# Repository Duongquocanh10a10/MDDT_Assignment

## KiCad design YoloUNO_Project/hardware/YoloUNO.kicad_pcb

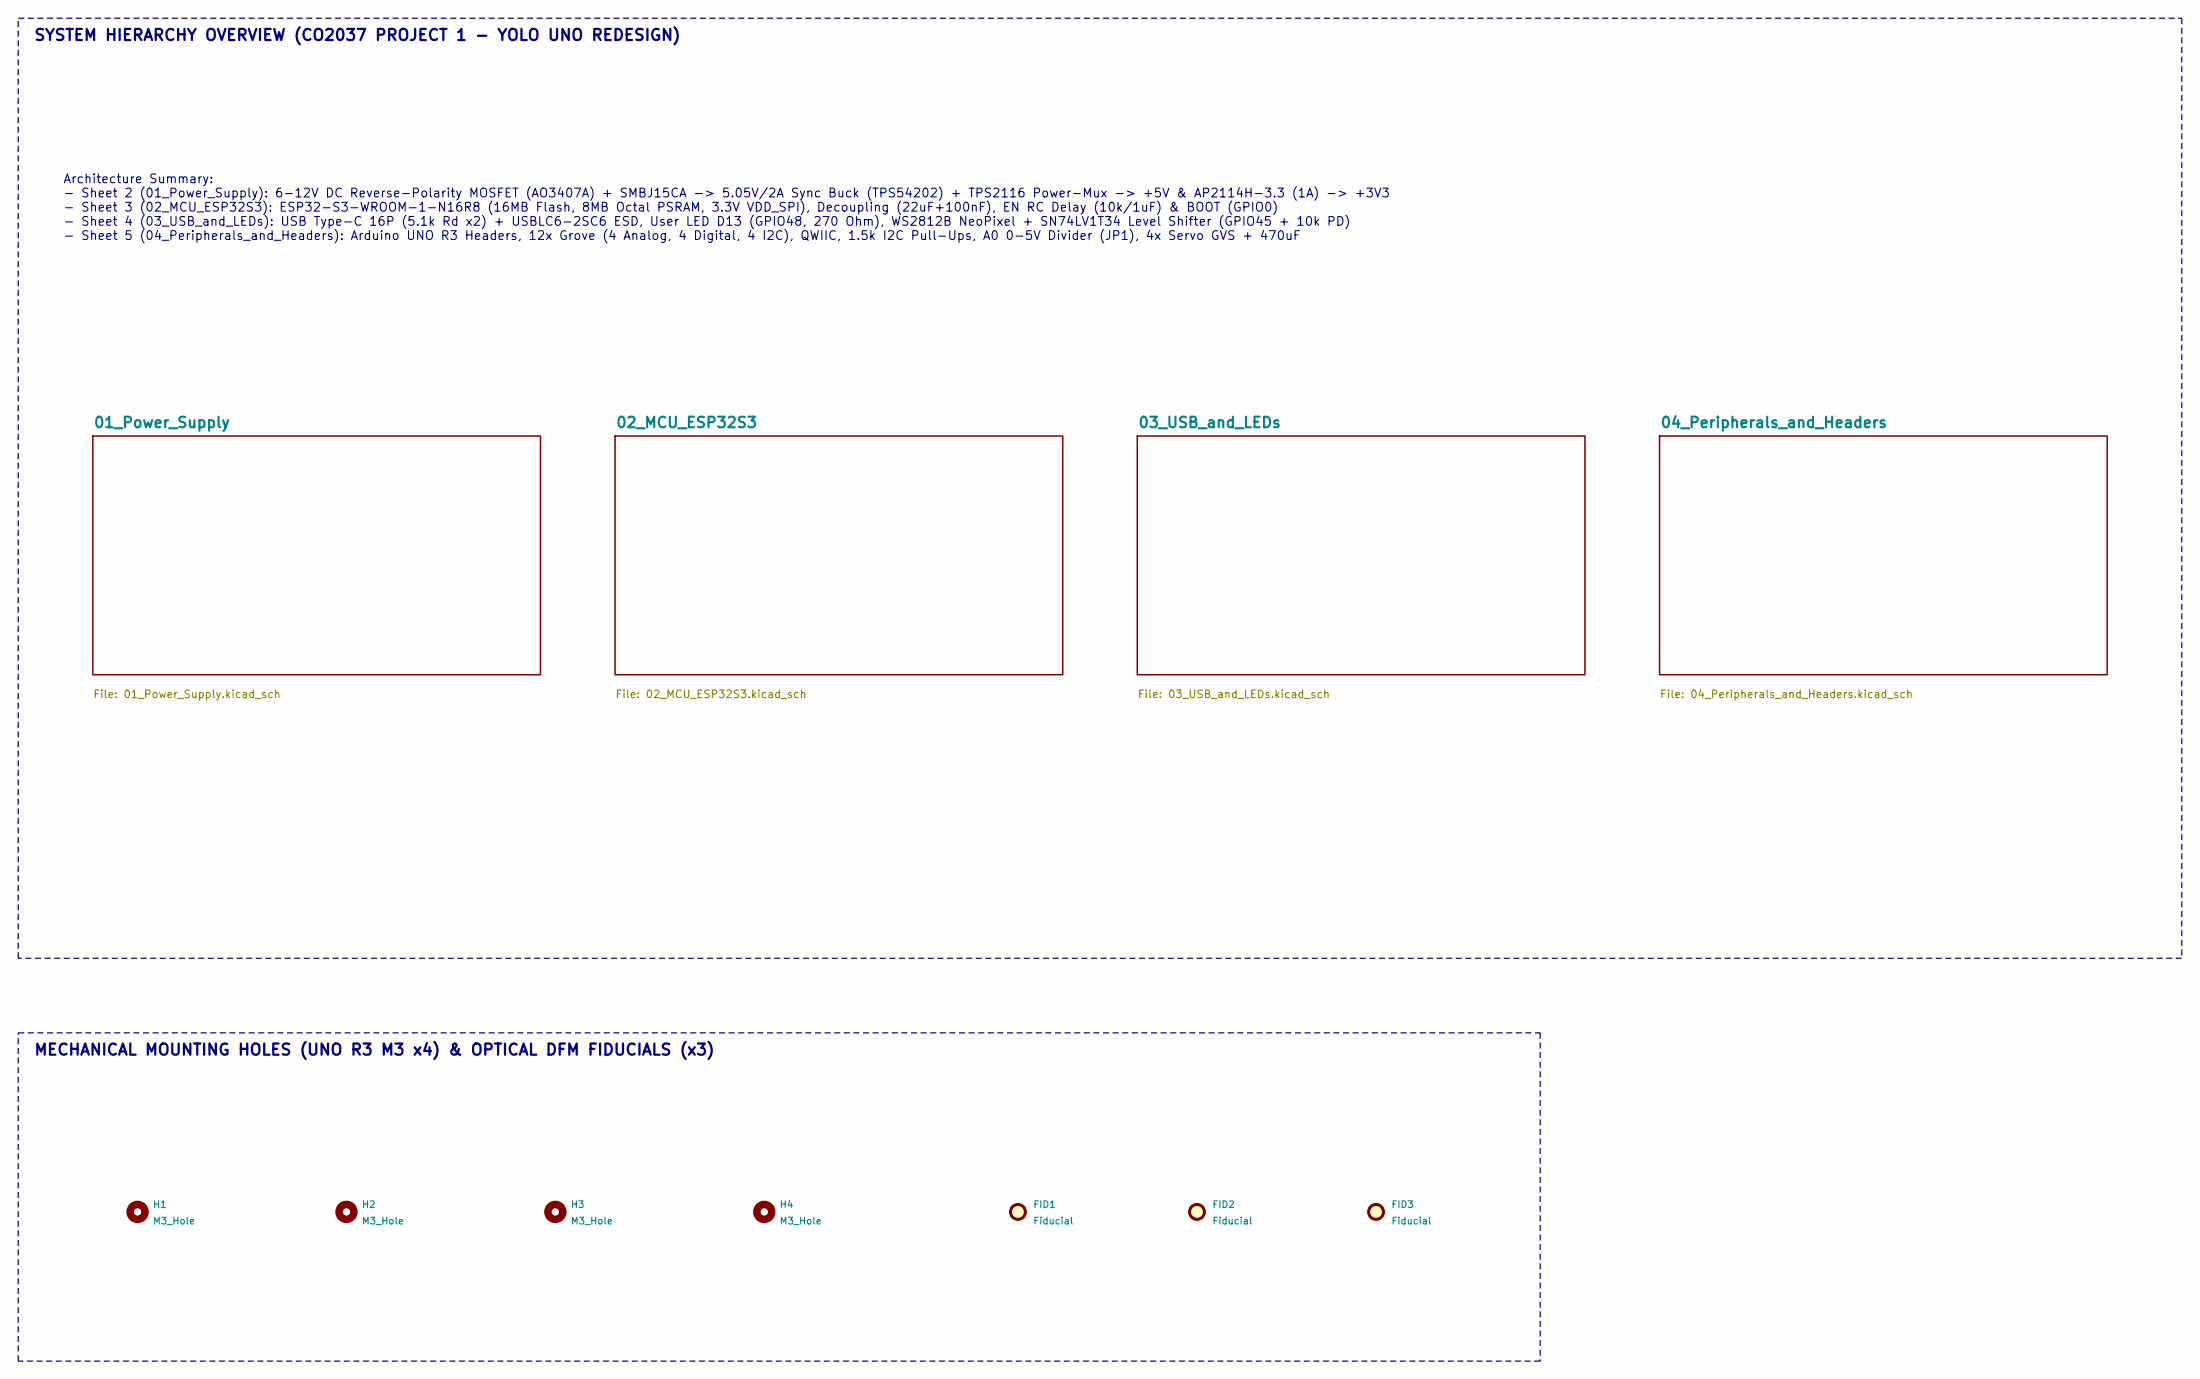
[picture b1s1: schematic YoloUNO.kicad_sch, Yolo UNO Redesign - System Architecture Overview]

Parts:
FID1, FID2, FID3: Fiducial; Fiducial_1mm_Mask2mm; MPN FIDUCIAL_1MM; LCSC N/A
H1, H2, H3, H4: M3_Hole; MountingHole_3.2mm_M3; MPN M3_NPTH_UNO_R3; LCSC N/A

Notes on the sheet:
SYSTEM HIERARCHY OVERVIEW (CO2037 PROJECT 1 - YOLO UNO REDESIGN)
Architecture Summary: - Sheet 2 (01_Power_Supply): 6-12V DC Reverse-Polarity MOSFET (AO3407A) + SMBJ15CA -> 5.05V/2A Sync Buck (TPS54202) + TPS2116 Power-Mux -> +5V & AP2114H-3.3 (1A) -> +3V3 - Sheet 3 (02_MCU_ESP32S3): ESP32-S3-WROOM-1-N16R8 (16MB Flash, 8MB Octal PSRAM, 3.3V VDD_SPI), Decoupling 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
MECHANICAL MOUNTING HOLES (UNO R3 M3 x4) & OPTICAL DFM FIDUCIALS (x3)

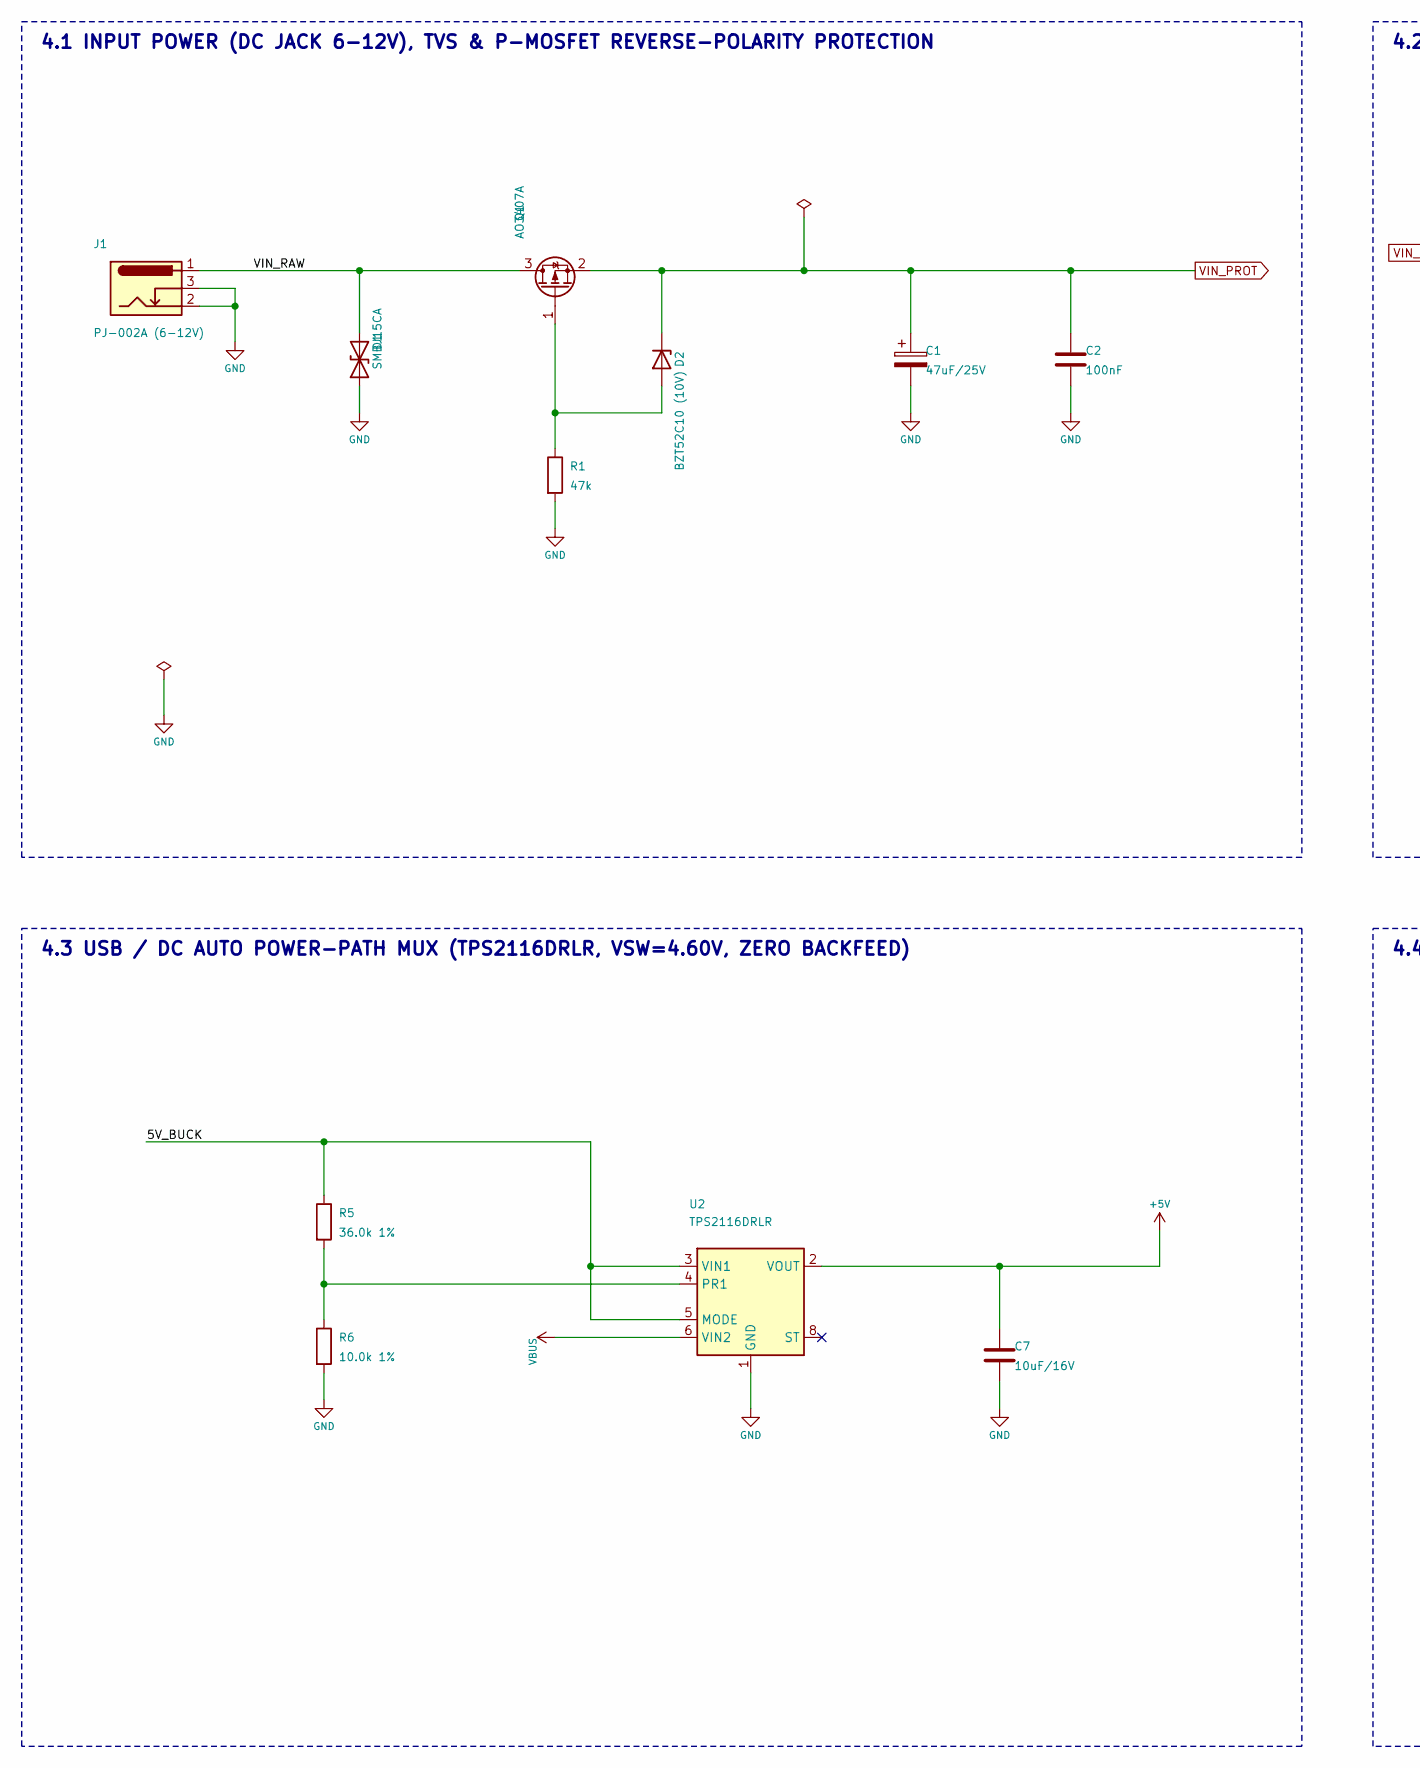
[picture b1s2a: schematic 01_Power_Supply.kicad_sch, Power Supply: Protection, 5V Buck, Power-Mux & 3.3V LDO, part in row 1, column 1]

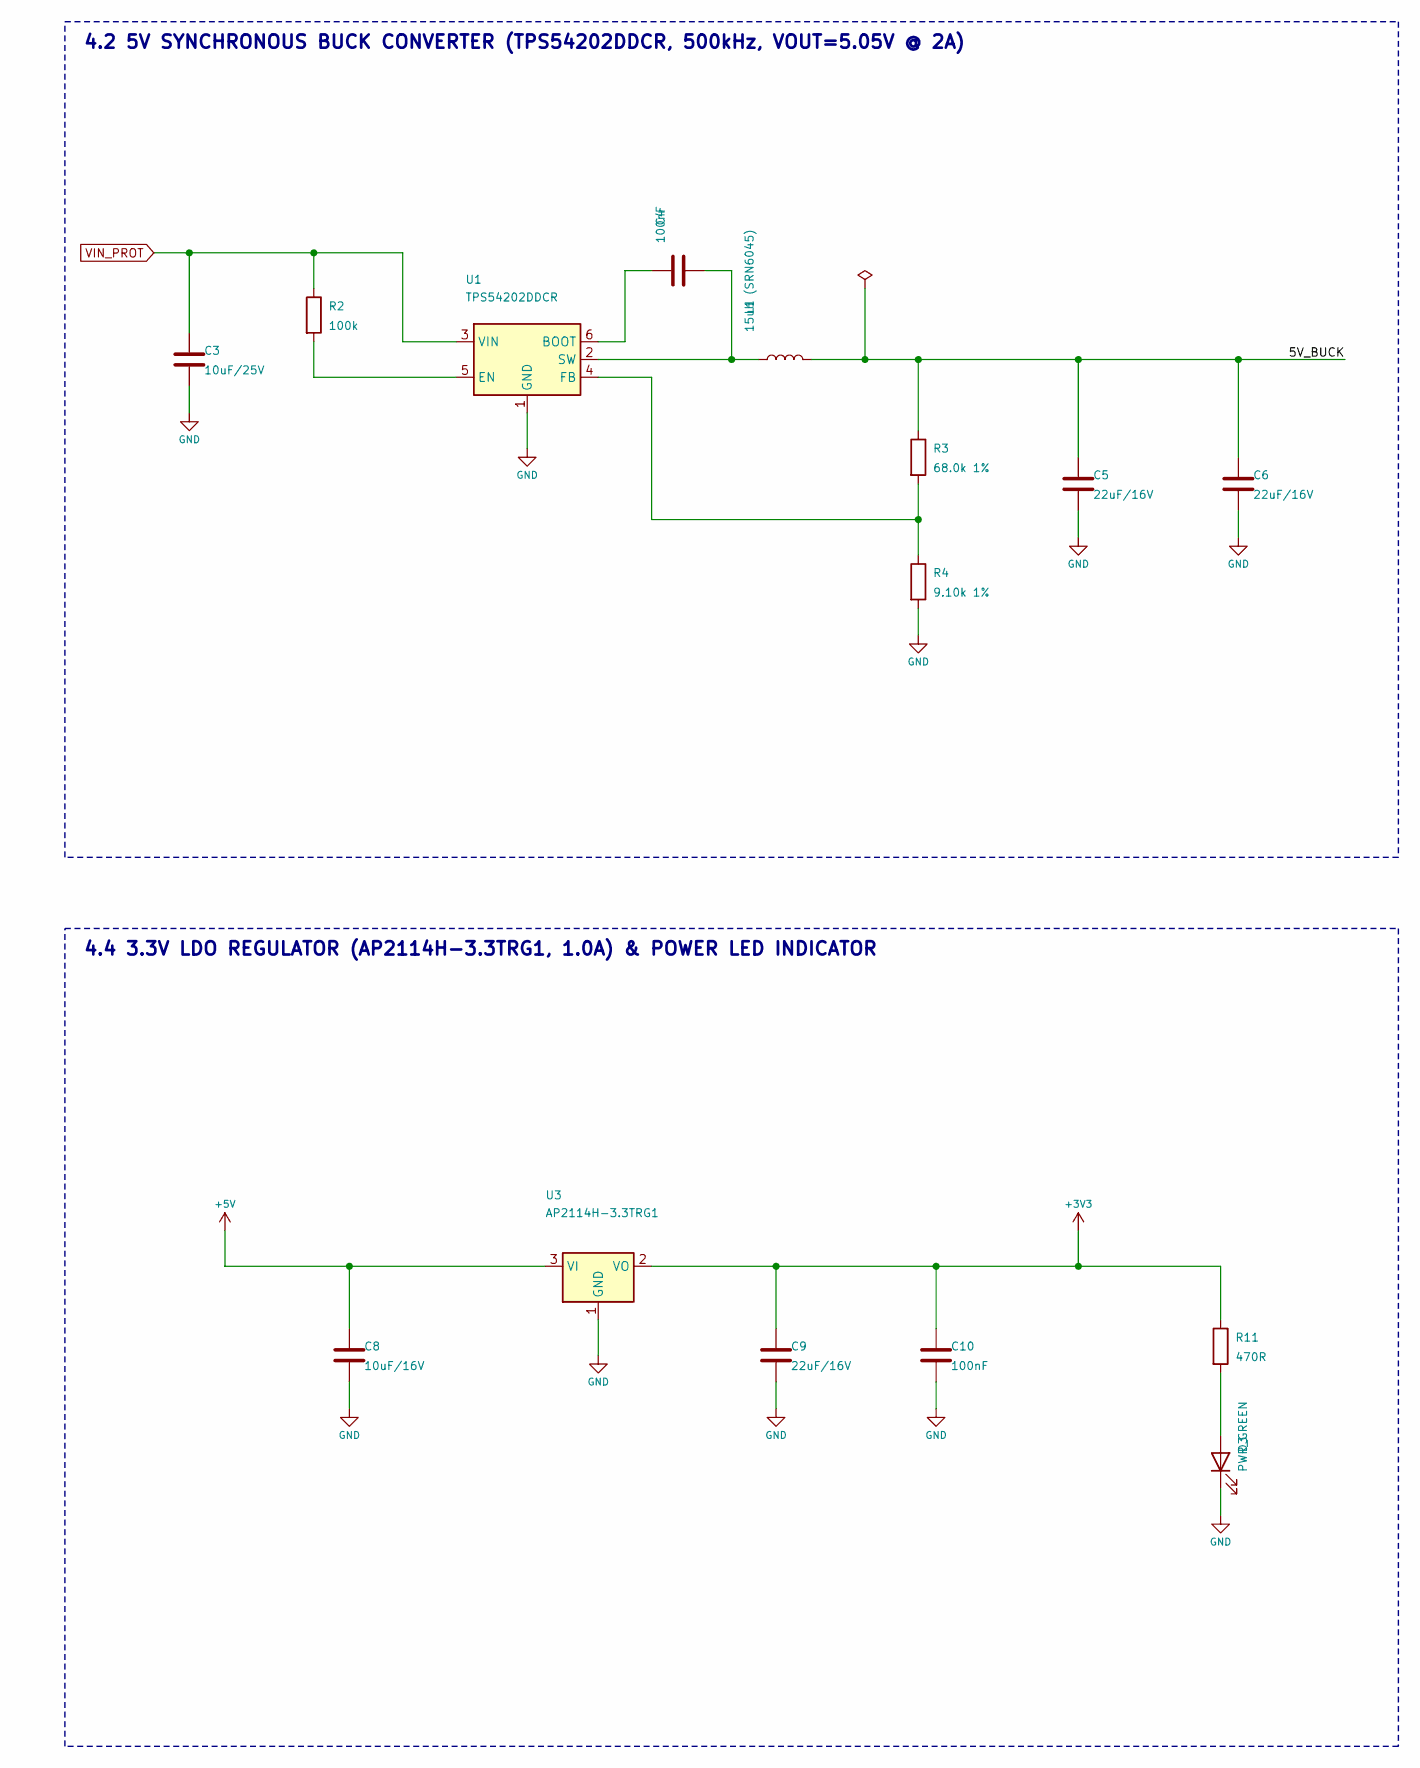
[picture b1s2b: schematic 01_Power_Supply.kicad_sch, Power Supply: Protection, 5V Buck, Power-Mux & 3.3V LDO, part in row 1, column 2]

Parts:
C1: 47uF/25V; CP_Elec_6.3x5.4; MPN EEE-FK1E470P; LCSC C72485
C2, C4, C10: 100nF; C_0603_1608Metric; MPN CL10B104KB8NNNC; LCSC C1591
C3: 10uF/25V; C_0805_2012Metric; MPN GRM21BR61E106KA73L; LCSC C15850
C5, C6, C9: 22uF/16V; C_0805_2012Metric; MPN GRM21BR61C226ME44L; LCSC C45783
C7, C8: 10uF/16V; C_0805_2012Metric; MPN CL21A106KOQNNNE; LCSC C17024
D1: SMBJ15CA; D_SMB; MPN SMBJ15CA; LCSC C123785
D2: BZT52C10 (10V); D_SOD-123; MPN BZT52C10-7-F; LCSC C81598
D3: PWR_GREEN; LED_0603_1608Metric; MPN 19-217/GHC-YR1S2/3T; LCSC C72043
J1: PJ-002A (6-12V); BarrelJack_CUI_PJ-102AH_Horizontal; MPN PJ-002A; LCSC C720477
L1: 15uH (SRN6045); L_Bourns_SRN6045TA; MPN SRN6045TA-150M; LCSC C169400
Q1: AO3407A; SOT-23-3; MPN AO3407A; LCSC C347475
R1: 47k; R_0603_1608Metric; MPN RC0603FR-0747KL; LCSC C25819
R2: 100k; R_0603_1608Metric; MPN RC0603FR-07100KL; LCSC C25803
R3: 68.0k 1%; R_0603_1608Metric; MPN RC0603FR-0768KL; LCSC C23231
R4: 9.10k 1%; R_0603_1608Metric; MPN RC0603FR-079K1L; LCSC C23268
R5: 36.0k 1%; R_0603_1608Metric; MPN RC0603FR-0736KL; LCSC C23146
R6: 10.0k 1%; R_0603_1608Metric; MPN RC0603FR-0710KL; LCSC C25804
R11: 470R; R_0603_1608Metric; MPN RC0603FR-07470RL; LCSC C23179
U1: TPS54202DDCR; SOT-23-6; MPN TPS54202DDCR; LCSC C128249
U2: TPS2116DRLR; SOT-583-8; MPN TPS2116DRLR; LCSC C2875184
U3: AP2114H-3.3TRG1; SOT-223-3_TabPin2; MPN AP2114H-3.3TRG1; LCSC C151275

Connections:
+3V3: C9.1, C10.1, R11.1, U3.2 (VO); also elsewhere on the board
+5V: C7.1, C8.1, U2.2 (VOUT), U2.7 (VOUT), U3.3 (VI); also elsewhere on the board
/01_Power_Supply/5V_BUCK: C5.1, C6.1, L1.2, R3.1, R5.1, U2.3 (VIN1), U2.5 (MODE)
/01_Power_Supply/VIN_RAW: D1.2 (A2), J1.1, Q1.3 (D)
unnamed: D2.2 (A), Q1.1 (G), R1.1
unnamed: D3.2 (A), R11.2
unnamed: C4.1, U1.6 (BOOT)
unnamed: R2.2, U1.5 (EN)
unnamed: R3.2, R4.1, U1.4 (FB)
unnamed: C4.2, L1.1, U1.2 (SW)
unnamed: R5.2, R6.1, U2.4 (PR1)
VBUS: U2.6 (VIN2); also elsewhere on the board
VIN_PROT: C1.1, C2.1, C3.1, D2.1 (K), Q1.2 (S), R2.1, U1.3 (VIN); also elsewhere on the board

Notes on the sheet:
4.1 INPUT POWER (DC JACK 6-12V), TVS & P-MOSFET REVERSE-POLARITY PROTECTION
4.2 5V SYNCHRONOUS BUCK CONVERTER (TPS54202DDCR, 500kHz, VOUT=5.05V @ 2A)
4.3 USB / DC AUTO POWER-PATH MUX (TPS2116DRLR, VSW=4.60V, ZERO BACKFEED)
4.4 3.3V LDO REGULATOR (AP2114H-3.3TRG1, 1.0A) & POWER LED INDICATOR

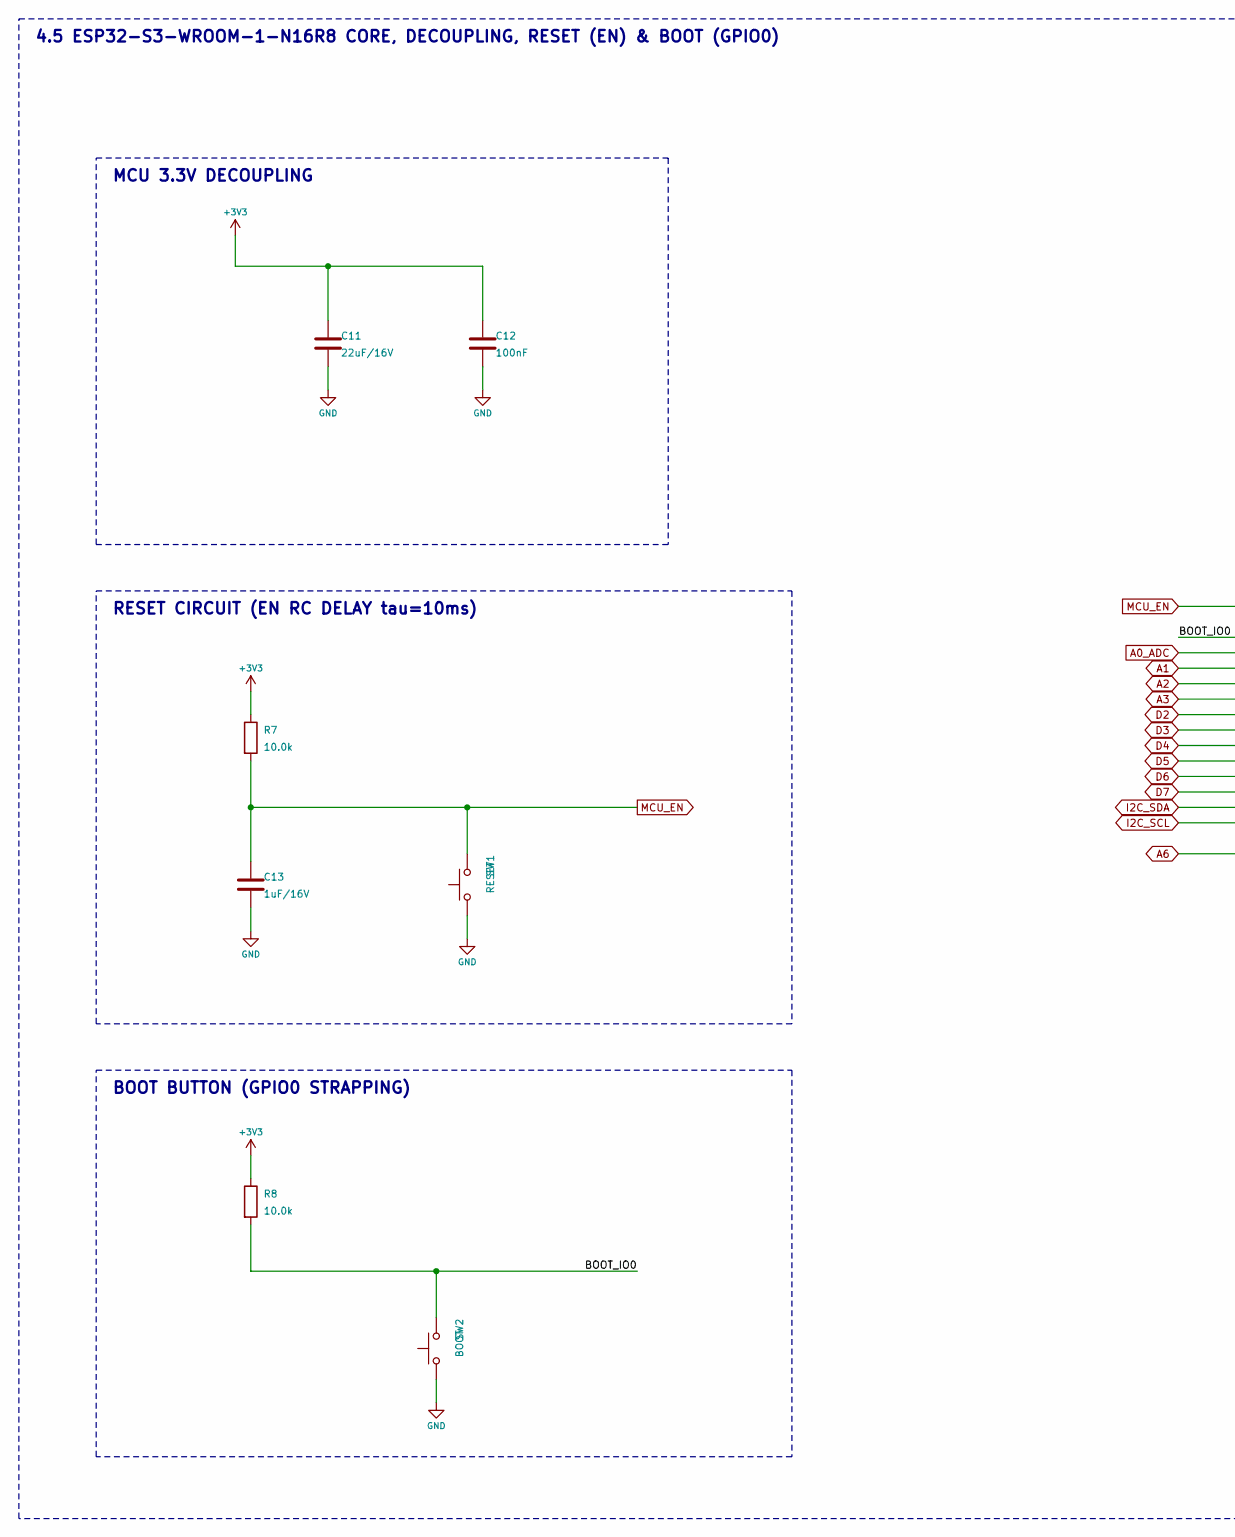
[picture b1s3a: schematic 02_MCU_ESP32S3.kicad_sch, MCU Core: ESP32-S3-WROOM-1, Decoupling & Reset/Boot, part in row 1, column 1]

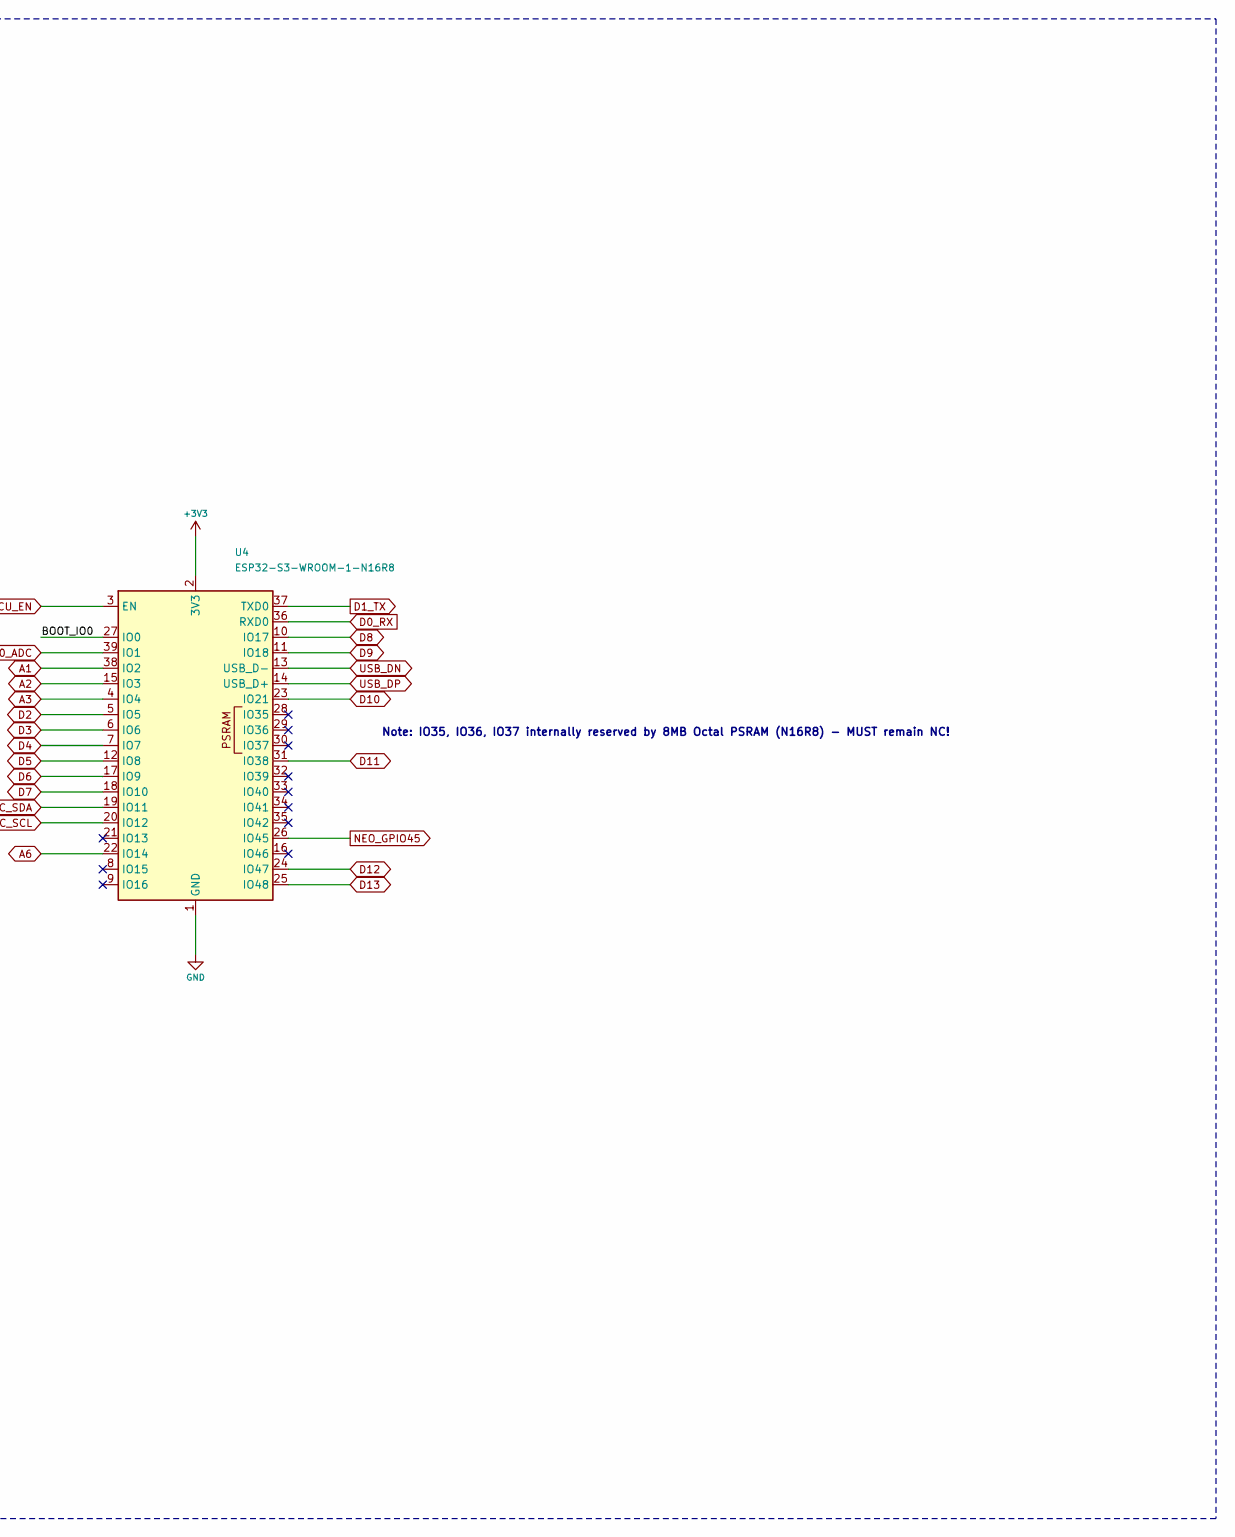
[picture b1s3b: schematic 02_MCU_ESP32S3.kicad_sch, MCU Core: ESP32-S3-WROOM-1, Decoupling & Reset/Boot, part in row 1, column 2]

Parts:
C11: 22uF/16V; C_0805_2012Metric; MPN GRM21BR61C226ME44L; LCSC C45783
C12: 100nF; C_0603_1608Metric; MPN CL10B104KB8NNNC; LCSC C1591
C13: 1uF/16V; C_0603_1608Metric; MPN CL10B105KO8NNNC; LCSC C15849
R7, R8: 10.0k; R_0603_1608Metric; MPN RC0603FR-0710KL; LCSC C25804
SW1: RESET; SW_Push_1P1T_XKB_TS-1187A; MPN TS-1187A-B-A-B; LCSC C318884
SW2: BOOT; SW_Push_1P1T_XKB_TS-1187A; MPN TS-1187A-B-A-B; LCSC C318884
U4: ESP32-S3-WROOM-1-N16R8; ESP32-S3-WROOM-1; MPN ESP32-S3-WROOM-1-N16R8; LCSC C2913202

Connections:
+3V3: C11.1, C12.1, R7.1, R8.1, U4.2 (3V3); also elsewhere on the board
/02_MCU_ESP32S3/BOOT_IO0: R8.2, SW2.2, U4.27 (IO0)
A0_ADC: U4.39 (IO1); also elsewhere on the board
A1: U4.38 (IO2); also elsewhere on the board
A2: U4.15 (IO3); also elsewhere on the board
A3: U4.4 (IO4); also elsewhere on the board
A6: U4.22 (IO14); also elsewhere on the board
D0_RX: U4.36 (RXD0); also elsewhere on the board
D1_TX: U4.37 (TXD0); also elsewhere on the board
D2: U4.5 (IO5); also elsewhere on the board
D3: U4.6 (IO6); also elsewhere on the board
D4: U4.7 (IO7); also elsewhere on the board
D5: U4.12 (IO8); also elsewhere on the board
D6: U4.17 (IO9); also elsewhere on the board
D7: U4.18 (IO10); also elsewhere on the board
D8: U4.10 (IO17); also elsewhere on the board
D9: U4.11 (IO18); also elsewhere on the board
D10: U4.23 (IO21); also elsewhere on the board
D11: U4.31 (IO38); also elsewhere on the board
D12: U4.24 (IO47); also elsewhere on the board
D13: U4.25 (IO48); also elsewhere on the board
I2C_SCL: U4.20 (IO12); also elsewhere on the board
I2C_SDA: U4.19 (IO11); also elsewhere on the board
MCU_EN: C13.1, R7.2, SW1.2, U4.3 (EN); also elsewhere on the board
NEO_GPIO45: U4.26 (IO45); also elsewhere on the board
USB_DN: U4.13 (USB_D-); also elsewhere on the board
USB_DP: U4.14 (USB_D+); also elsewhere on the board

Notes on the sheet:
4.5 ESP32-S3-WROOM-1-N16R8 CORE, DECOUPLING, RESET (EN) & BOOT (GPIO0)
Note: IO35, IO36, IO37 internally reserved by 8MB Octal PSRAM (N16R8) - MUST remain NC!
MCU 3.3V DECOUPLING
RESET CIRCUIT (EN RC DELAY tau=10ms)
BOOT BUTTON (GPIO0 STRAPPING)

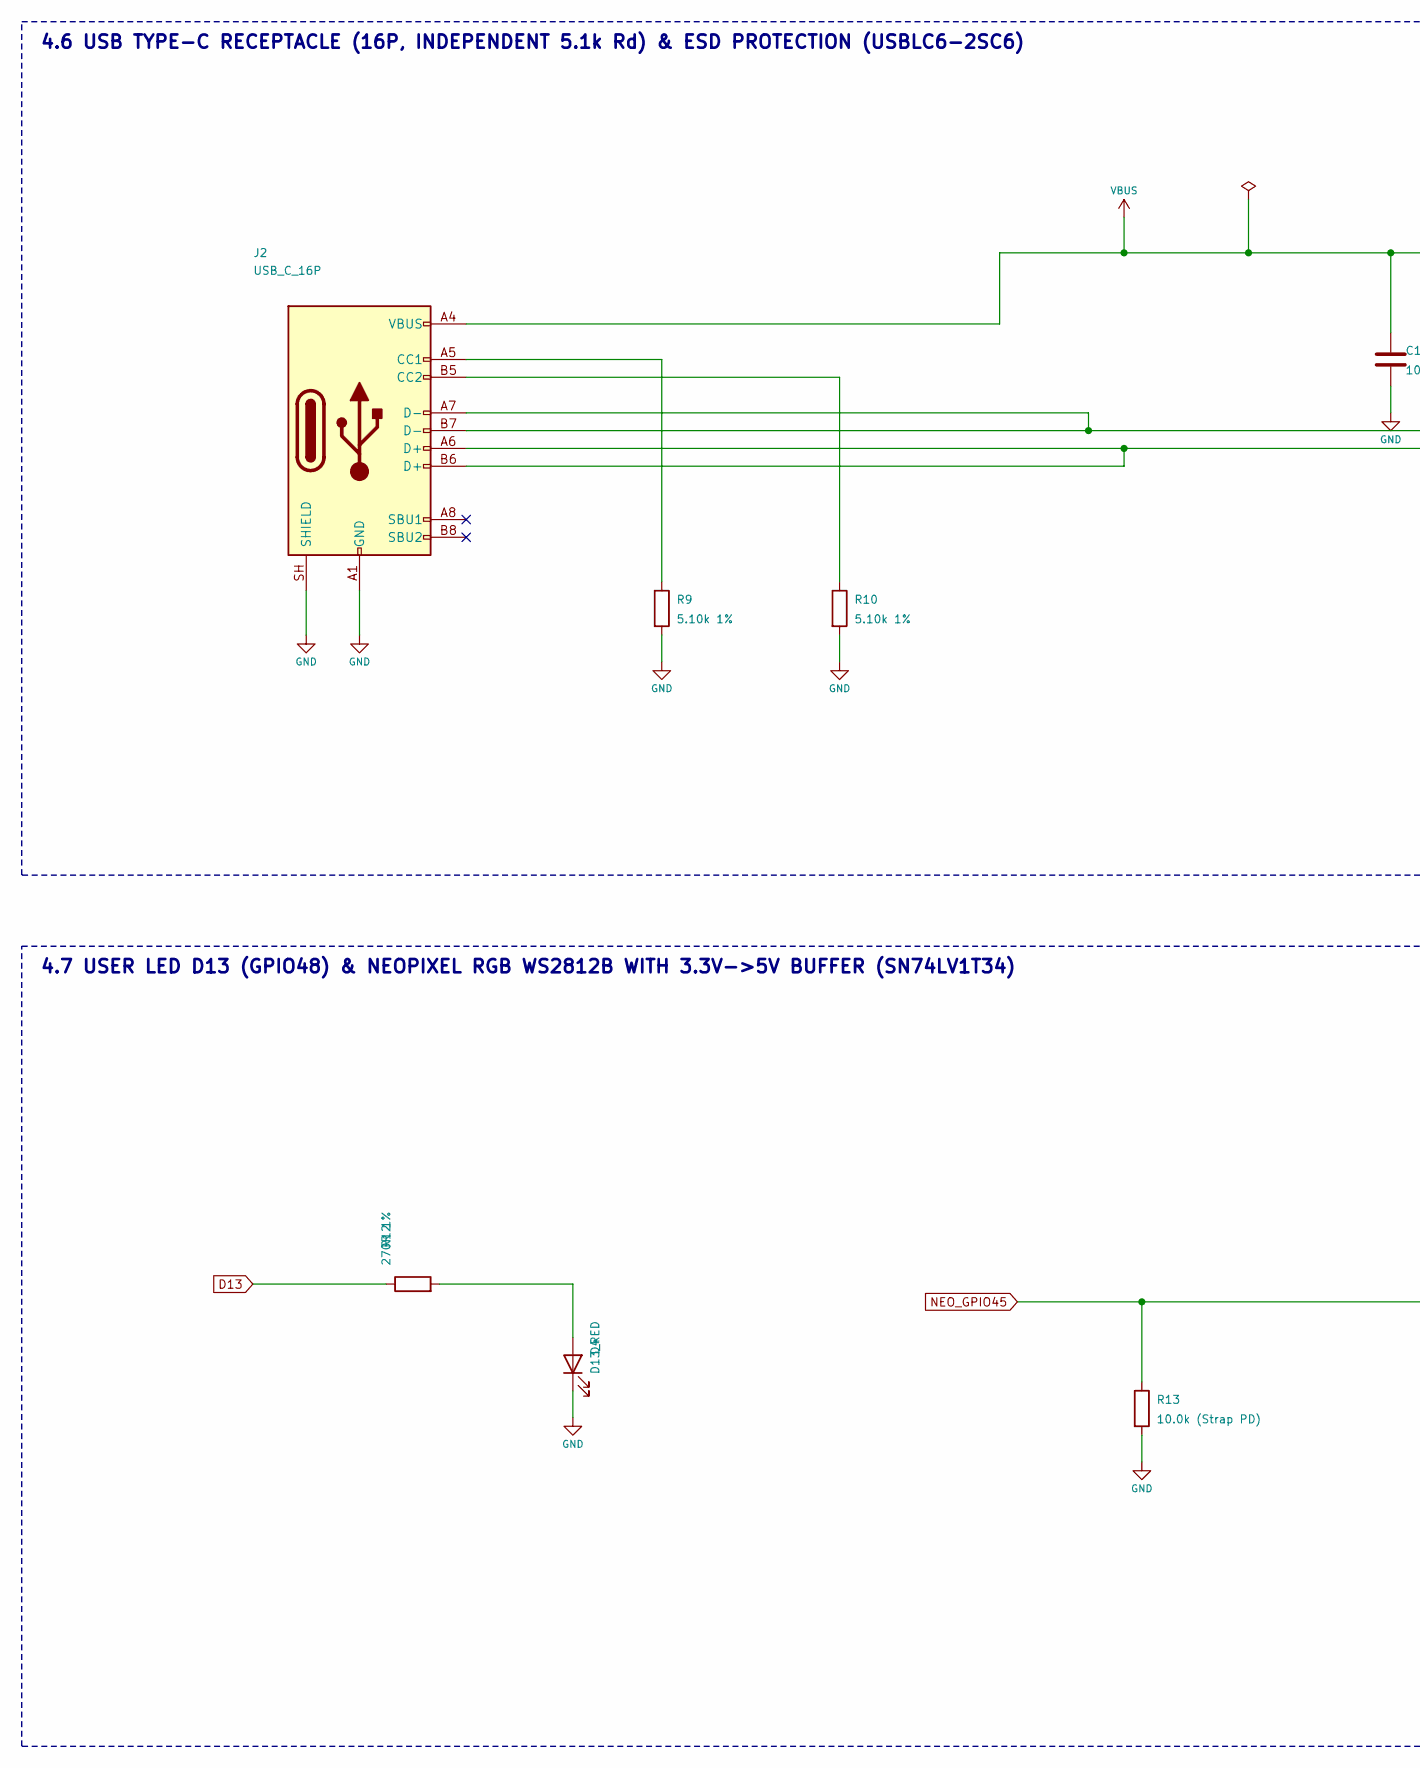
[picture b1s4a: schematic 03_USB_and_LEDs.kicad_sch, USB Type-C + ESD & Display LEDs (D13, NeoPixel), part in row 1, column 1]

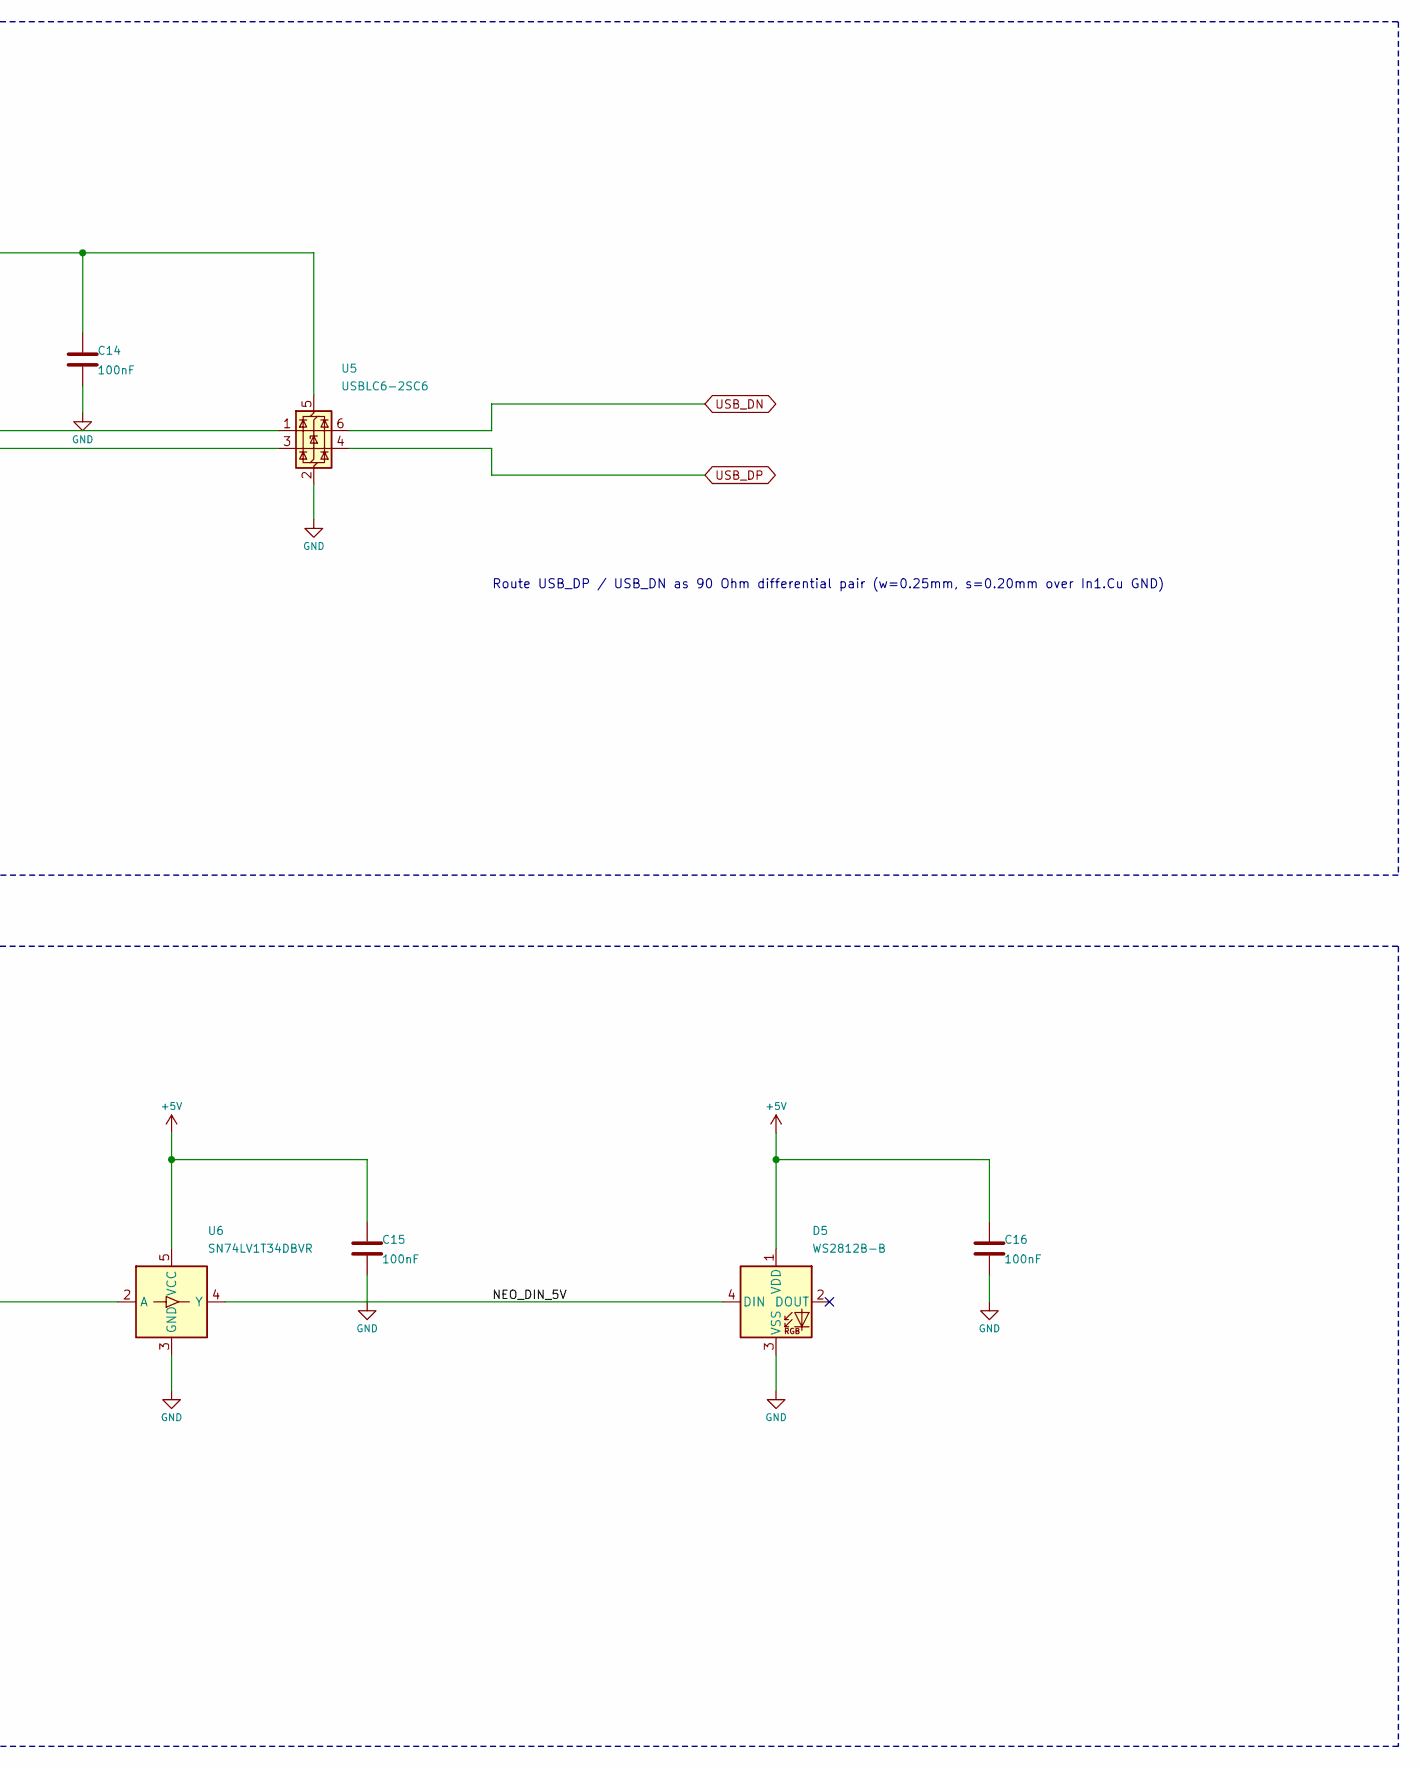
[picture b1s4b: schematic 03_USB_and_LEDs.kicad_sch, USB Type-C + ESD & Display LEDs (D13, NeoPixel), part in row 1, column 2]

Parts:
C14, C15, C16: 100nF; C_0603_1608Metric; MPN CL10B104KB8NNNC; LCSC C1591
D4: D13_RED; LED_0603_1608Metric; MPN 19-217/R6C-AL1M2VY/3T; LCSC C2286
D5: WS2812B-B; LED_WS2812B_PLCC4_5.0x5.0mm_P3.2mm; MPN WS2812B-B/W; LCSC C114586
J2: USB_C_16P; USB_C_Receptacle_HRO_TYPE-C-31-M-12; MPN TYPE-C-31-M-12; LCSC C165948
R9, R10: 5.10k 1%; R_0603_1608Metric; MPN RC0603FR-075K1L; LCSC C23186
R12: 270R 1%; R_0603_1608Metric; MPN RC0603FR-07270RL; LCSC C22966
R13: 10.0k (Strap PD); R_0603_1608Metric; MPN RC0603FR-0710KL; LCSC C25804
U5: USBLC6-2SC6; SOT-23-6; MPN USBLC6-2SC6; LCSC C7519
U6: SN74LV1T34DBVR; SOT-23-5; MPN SN74LV1T34DBVR; LCSC C100018

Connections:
+5V: C15.1, C16.1, D5.1 (VDD), U6.5 (VCC); also elsewhere on the board
D13: R12.1; also elsewhere on the board
NEO_GPIO45: R13.1, U6.2 (A); also elsewhere on the board
unnamed: D4.2 (A), R12.2
unnamed: J2.A5 (CC1), R9.1
unnamed: J2.B5 (CC2), R10.1
unnamed: J2.A6 (D+), J2.B6 (D+), U5.3 (I/O2)
unnamed: J2.A7 (D-), J2.B7 (D-), U5.1 (I/O1)
USB_DN: U5.6 (I/O1); also elsewhere on the board
USB_DP: U5.4 (I/O2); also elsewhere on the board
VBUS: C14.1, J2.A4 (VBUS), J2.A9 (VBUS), J2.B4 (VBUS), J2.B9 (VBUS), U5.5 (VBUS); also elsewhere on the board

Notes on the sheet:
4.6 USB TYPE-C RECEPTACLE (16P, INDEPENDENT 5.1k Rd) & ESD PROTECTION (USBLC6-2SC6)
Route USB_DP / USB_DN as 90 Ohm differential pair (w=0.25mm, s=0.20mm over In1.Cu GND)
4.7 USER LED D13 (GPIO48) & NEOPIXEL RGB WS2812B WITH 3.3V->5V BUFFER (SN74LV1T34)

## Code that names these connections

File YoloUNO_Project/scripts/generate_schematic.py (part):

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                 68.58, 68.58, rot=90, mpn="SMBJ15CA", lcsc="C123785",
                 ref_offset=(2.54, -1.27), val_offset=(2.54, 1.524))
s_pwr.add_wire(j1_p1[0], j1_p1[1], 68.58, j1_p1[1])
s_pwr.add_label("VIN_RAW", 53.34, j1_p1[1])
s_pwr.add_wire(68.58, j1_p1[1], *d1.pin_xy("2"))
s_pwr.add_junction(68.58, j1_p1[1])
s_pwr.tie_gnd(*d1.pin_xy("1"), 3.81)
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s_pwr.add_junction(170.18, 55.88)
s_pwr.tie_gnd(*c2.pin_xy("2"), 3.81)

s_pwr.add_glabel("VIN_PROT", 187.96, 55.88, rot=0, shape="output")

s_pwr.add_pwr("GND", 40.64, 119.38, rot=0)
s_pwr.add_wire(40.64, 119.38, 40.64, 114.3)
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u1_sw = u1.pin_xy("2")
u1_fb = u1.pin_xy("4")

s_pwr.add_glabel("VIN_PROT", 226.06, 53.34, rot=180, shape="input")
s_pwr.add_wire(226.06, 53.34, 261.62, 53.34)
s_pwr.add_wire(261.62, 53.34, 261.62, u1_vin[1])
s_pwr.add_wire(261.62, u1_vin[1], u1_vin[0], u1_vin[1])
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    "14": ("USB_DP", "bidirectional"),
    "23": ("D10", "bidirectional"),
    "31": ("D11", "bidirectional"),
    "26": ("NEO_GPIO45", "output"),
    "24": ("D12", "bidirectional"),
    "25": ("D13", "bidirectional"),
}
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en_y = 149.86
s_mcu.add_wire(*r7.pin_xy("2"), 58.42, en_y)
s_mcu.add_wire(58.42, en_y, 121.92, en_y)
s_mcu.add_glabel("MCU_EN", 121.92, en_y, rot=0, shape="output")

c13 = s_mcu.place("YoloUNO:C", "C13", "1uF/16V", "YoloUNO:C_0603_1608Metric",
                  58.42, 162.56, rot=0, mpn="CL10B105KO8NNNC", lcsc="C15849")
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boot_y = 226.06
s_mcu.add_wire(*r8.pin_xy("2"), 58.42, boot_y)
s_mcu.add_wire(58.42, boot_y, 121.92, boot_y)
s_mcu.add_label("BOOT_IO0", 121.92, boot_y, rot=180)

sw2 = s_mcu.place("YoloUNO:TS-1187A", "SW2", "BOOT", "YoloUNO:SW_Push_1P1T_XKB_TS-1187A",
                  88.9, 238.76, rot=90, mpn="TS-1187A-B-A-B", lcsc="C318884",
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s_usb.add_wire(*u5.pin_xy("6"), 274.32, 78.74)
s_usb.add_wire(274.32, 78.74, 274.32, 74.93)
s_usb.add_wire(274.32, 74.93, 304.8, 74.93)
s_usb.add_glabel("USB_DN", 304.8, 74.93, rot=0, shape="bidirectional")

s_usb.add_wire(*u5.pin_xy("4"), 274.32, 81.28)
s_usb.add_wire(274.32, 81.28, 274.32, 85.09)
s_usb.add_wire(274.32, 85.09, 304.8, 85.09)
s_usb.add_glabel("USB_DP", 304.8, 85.09, rot=0, shape="bidirectional")
s_usb.add_note("Route USB_DP / USB_DN as 90 Ohm differential pair (w=0.25mm, s=0.20mm over In1.Cu GND)", 274.32, 101.6, size=1.3)


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s_usb.add_wire(99.06, 200.66, *d4.pin_xy("2"))
s_usb.tie_gnd(*d4.pin_xy("1"), 3.81)

s_usb.add_glabel("NEO_GPIO45", 162.56, 203.2, rot=180, shape="input")
r13 = s_usb.place("YoloUNO:R", "R13", "10.0k (Strap PD)", "YoloUNO:R_0603_1608Metric",
                  180.34, 218.44, rot=0, mpn="RC0603FR-0710KL", lcsc="C25804")
u6 = s_usb.place("YoloUNO:SN74LV1T34DBVR", "U6", "SN74LV1T34DBVR", "YoloUNO:SOT-23-5",
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                 314.96, 203.2, rot=0, mpn="WS2812B-B/W", lcsc="C114586",
                 ref_offset=(5.08, -10.16), val_offset=(5.08, -7.62))
s_usb.add_wire(*u6.pin_xy("4"), *d5.pin_xy("4"))
s_usb.add_label("NEO_DIN_5V", 274.32, 203.2)
s_usb.add_nc(*d5.pin_xy("2"))
s_usb.tie_gnd(*d5.pin_xy("3"), 5.08)

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# --- Sub-box B: A0 0-5V Analog Conditioning (Q[10]: JP1 rot=0 so Bridged12 = Direct 3.3V default!) ---
s_per.add_box("4.8B A0 0-5V CONDITIONING (Q[10])", 15.24, 182.88, 129.54, 266.7)

# JP1 at rot=0: Pin 1=(-5.08,0) [LEFT=Direct A0_RAW, Bridged12 default!], Pin 3=(5.08,0) [RIGHT=5V Scaled], Pin 2=(0,-3.81)->(sx, sy+3.81) [BOTTOM=A0_ADC]
jp1 = s_per.place("YoloUNO:SolderJumper_3_Bridged12", "JP1", "A0_3V3/5V", "YoloUNO:SolderJumper-3_P1.3mm_Bridged12_Pad1.0x1.5mm",
                  63.5, 208.28, rot=0, mpn="SJ-3-1.3MM", lcsc="N/A",
                  ref_offset=(-5.08, -6.35), val_offset=(-5.08, -3.81))
# A0_RAW enters at (25.4, 208.28) -> connects straight into JP1 Pin 1 (58.42, 208.28), and branches UP at x=43.18 to R16/R17 on the right!
# Even simpler: branch UP at x=43.18 -> y=195.58 -> x=93.98 -> DOWN through R16 (6.8k) -> midpoint (93.98, 208.28) -> JP1 Pin 3 (68.58, 208.28), and R17 (10k) below!
s_per.add_wire(27.94, 208.28, *jp1.pin_xy("1"))
s_per.add_label("A0_RAW", 27.94, 208.28, rot=0)

s_per.add_wire(43.18, 208.28, 43.18, 194.31)
s_per.add_junction(43.18, 208.28)
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s_per.add_junction(96.52, 208.28)
s_per.tie_gnd(*r17.pin_xy("2"), 3.81)

# JP1 Pin 2 (63.5, 212.09) -> y=226.06 -> C17 (100nF) + A0_ADC
s_per.add_wire(*jp1.pin_xy("2"), 63.5, 226.06)
s_per.add_wire(63.5, 226.06, 81.28, 226.06)
s_per.add_glabel("A0_ADC", 81.28, 226.06, rot=0, shape="output")
c17 = s_per.place("YoloUNO:C", "C17", "100nF", "YoloUNO:C_0603_1608Metric",
                  63.5, 238.76, rot=0, mpn="CL10B104KB8NNNC", lcsc="C1591")
s_per.add_wire(63.5, 226.06, *c17.pin_xy("1"))
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s_per.add_wire(152.4, p3y, p3x, p3y)
s_per.add_wire(144.78, p3y, 152.4, p3y)
s_per.add_junction(152.4, p3y)
s_per.add_glabel("I2C_SDA", 144.78, p3y, rot=180, shape="bidirectional")

p4x, p4y = j15.pin_xy("4")
s_per.add_wire(175.26, r15.pin_xy("2")[1], 175.26, p4y)
s_per.add_wire(175.26, p4y, p4x, p4y)
s_per.add_wire(144.78, p4y, 175.26, p4y)
s_per.add_junction(175.26, p4y)
s_per.add_glabel("I2C_SCL", 144.78, p4y, rot=180, shape="bidirectional")

s_per.tie_gnd(*j15.pin_xy("MP"), 3.81)

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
